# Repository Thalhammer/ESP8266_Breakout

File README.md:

# ESP8266_Breakout
A breakout board for ESP8266 ESP12-F Modules

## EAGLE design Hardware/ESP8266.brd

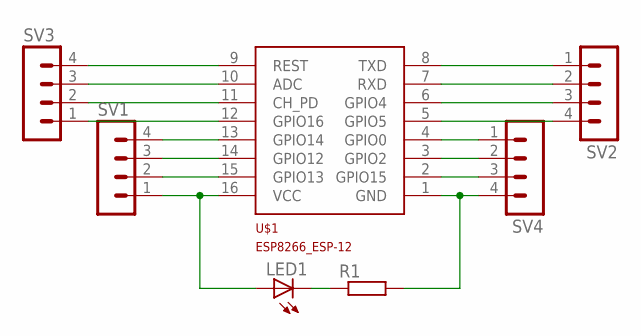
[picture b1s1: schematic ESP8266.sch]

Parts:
LED1: LEDSML0805; SML0805
R1: R-EU_R0805; R0805
SV1, SV2, SV3, SV4: MA04-1
U$1: ESP8266_ESP-12; ESP8266-ESP12

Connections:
unnamed: LED1.A, SV1.1, U$1.16 (VCC)
unnamed: SV1.2, U$1.15 (GPIO13)
unnamed: SV1.3, U$1.14 (GPIO12)
unnamed: SV1.4, U$1.13 (GPIO14)
unnamed: SV3.1, U$1.12 (GPIO16)
unnamed: SV3.2, U$1.11 (CH_PD)
unnamed: SV3.3, U$1.10 (ADC)
unnamed: SV3.4, U$1.9 (REST)
unnamed: R1.2, SV4.4, U$1.1 (GND)
unnamed: SV4.3, U$1.2 (GPIO15)
unnamed: SV4.2, U$1.3 (GPIO2)
unnamed: SV4.1, U$1.4 (GPIO0)
unnamed: SV2.4, U$1.5 (GPIO5)
unnamed: SV2.3, U$1.6 (GPIO4)
unnamed: SV2.2, U$1.7 (RXD)
unnamed: SV2.1, U$1.8 (TXD)
unnamed: LED1.C, R1.1

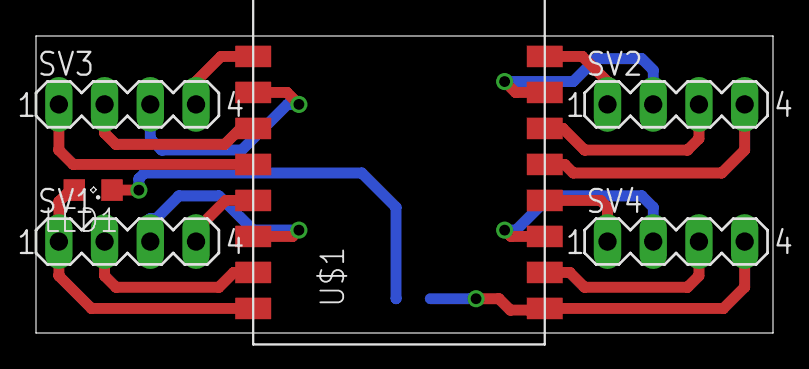
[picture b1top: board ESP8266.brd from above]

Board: 2 copper layers, 40.9 x 16.5 mm, 7 parts (1 on the bottom side), 17 nets.

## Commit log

2016-06-26 Initial board version
